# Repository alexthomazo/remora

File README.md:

Remora
======

Contrôleur fil pilote permettant de contrôler 7 zones et un relai.

Basé sur ESP32 et ESPHome.

Version 2.0 de Remora basé sur https://github.com/tducret/programmateur-fil-pilote-wifi/tree/master

Fonctionnalités
---------------

 * ESP32 Mini D1
 * MCP23017 pour le contrôle des 7 zones et du relai
 * Port ethernet optionnel
 * Connecteur I2C pour ecran OLED
 * Relai permettant le contrôle d'un connecteur heures pleines/creuses

Changements depuis la version 1.3
---------------------------------

 * Ajout
   - Ajout d'un condensateur 47u en entrée pour filtrage
   - Port Ethernet (optionnel)
   - Snubber RC pour maximiser la durée de vie du relai
   - LED "relai" indépendante

 * Modification
   - Base ESP32 D1 mini
   - MCP23017 en SMD pour gain de place
   - Téléinfo basée sur Denky D4 avec résistance variable et LED
   - Nouvelle ref opto fils pilotes TLP267J
   - Nouvelle ref relai G5Q-1 (mécanique moins cher SSR) 
   
 * Suppression
   - récepteurs sans fils 433 et 868Mhz
   - connecteurs SPI et Groove I2C
   - LED 3mm RGB

Les composants SMD (hors partie LAN) sont prévus pour être soudés au fer.

Schématique
-----------

Board
-----

Case
----

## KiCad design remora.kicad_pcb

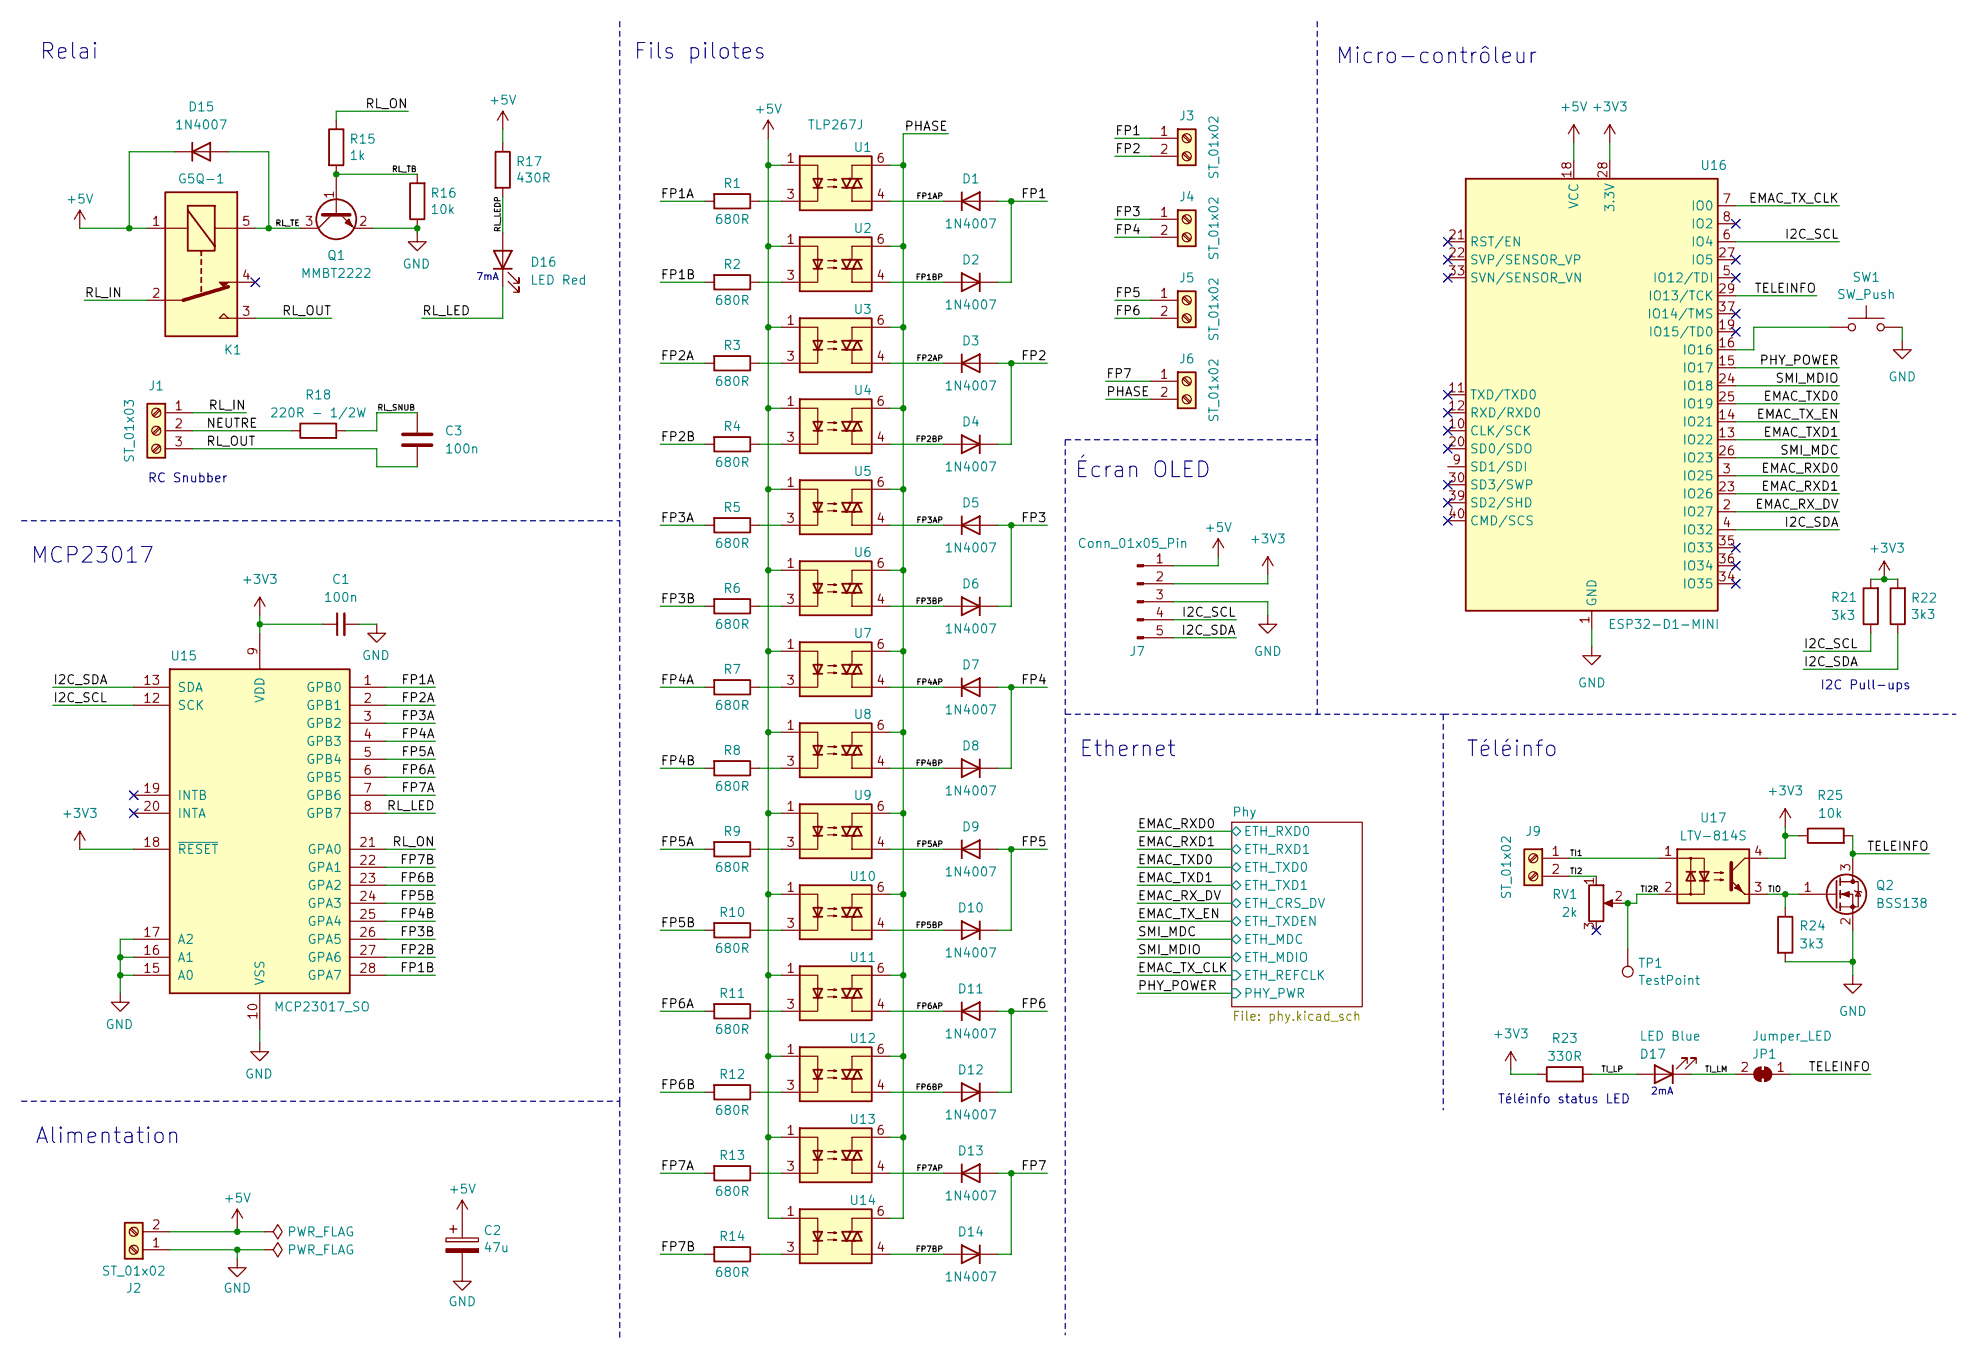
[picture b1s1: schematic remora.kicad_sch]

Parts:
C1: 100n; C_0805_2012Metric_Pad1.18x1.45mm_HandSolder; Mouser# 603-CC805KRX7R9BB104; LCSC# C49678
C2: 47u; C_Elec_6.3x5.4; Mouser# 80-EDK476M035A9GAA; LCSC# C131122
C3: 100n; C_Rect_L11.5mm_W5.6mm_P10.00mm_MKT; LCSC# C506867
D1, D2, D3, D4, D5, D6, D7, D8, D9, D10, D11, D12, D13, D14, D15: 1N4007; D_SOD-123FL; Mouser# 863-NRVS1MFL; LCSC# C727082
D16: LED Red; LED_0805_2012Metric_Pad1.15x1.40mm_HandSolder; Mouser# 743-IN-S85AT5UW; LCSC# C7371913
D17: LED Blue; LED_0805_2012Metric_Pad1.15x1.40mm_HandSolder; Mouser# 743-IN-S85AT5B; LCSC# C434433
J1: ST_01x03; TerminalBlock_Phoenix_PT-1,5-3-5.0-H_1x03_P5.00mm_Horizontal; Mouser# 490-TB003-500-P03BE; LCSC# C5188464
J2, J3, J4, J5, J6, J9: ST_01x02; TerminalBlock_Phoenix_PT-1,5-2-5.0-H_1x02_P5.00mm_Horizontal; Mouser# 490-TB003-500-P02BE; LCSC# C5188463
J7: Conn_01x05_Pin; PinHeader_1x05_P2.54mm_Vertical; Mouser# 200-EW0509TS300; LCSC# C492404
JP1: Jumper_LED; SolderJumper-2_P1.3mm_Bridged_RoundedPad1.0x1.5mm
K1: G5Q-1; Relay_SPDT_Omron-G5Q-1; Mouser# 769-ALQ105; LCSC# C719517
Q1: MMBT2222; SOT-23; Mouser# 771-MMBT2222A215; LCSC# C916372
Q2: BSS138; SOT-23; Mouser# 771-BSS138P215; LCSC# C713688
R1, R2, R3, R4, R5, R6, R7, R8, R9, R10, R11, R12, R13, R14: 680R; R_0805_2012Metric_Pad1.20x1.40mm_HandSolder; Mouser# 603-RC0805FR-07680RL; LCSC# C114549
R15: 1k; R_0805_2012Metric_Pad1.20x1.40mm_HandSolder; Mouser# 603-RC0805FR-071KL
R16, R25: 10k; R_0805_2012Metric_Pad1.20x1.40mm_HandSolder; Mouser# 603-RC0805FR-0710KL
R17: 430R; R_0805_2012Metric_Pad1.20x1.40mm_HandSolder; Mouser# 603-RC0805FR-07430RL
R18: 220R - 1/2W; R_Axial_DIN0309_L9.0mm_D3.2mm_P12.70mm_Horizontal; Mouser# 603-CFR-50JR-52-220R; LCSC# C119410
R21, R22, R24: 3k3; R_0805_2012Metric_Pad1.20x1.40mm_HandSolder; Mouser# 603-RC0805FR-073K3L
R23: 330R; R_0805_2012Metric_Pad1.20x1.40mm_HandSolder; Mouser# 603-RC0805FR-07330RL; LCSC# C105878
RV1: 2k; Potentiometer_Bourns_TC33X_Vertical; Mouser# 652-TC33X-2-202E; LCSC# C128549
SW1: SW_Push; SW_Push_1P1T_NO_6x6mm_H9.5mm; Mouser# 179-TS046655BK160SMT; LCSC# C255812
TP1: TestPoint; TestPoint_THTPad_D1.0mm_Drill0.5mm
U1, U2, U3, U4, U5, U6, U7, U8, U9, U10, U11, U12, U13, U14: TLP267J; MFSOP6-4_4.4x3.6mm_P1.27mm; Mouser# 757-TLP267JE; LCSC# C393892
U15: MCP23017_SO; SOIC-28W_7.5x17.9mm_P1.27mm; Mouser# 579-MCP23017-E/SO; LCSC# C629440
U16: ESP32-D1-MINI
U17: LTV-814S; DIP-4_W8.89mm_SMDSocket_LongPads; Mouser# 859-LTV-814S; LCSC# C125118

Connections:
+3V3: C1.1, J7.2, R21.2, R22.2, R23.1, R25.1, U15.9 (VDD), U15.18 (~RESET), U16.28 (3.3V), U17.4; also elsewhere on the board
+5V: C2.1, D15.1 (K), J2.2, J7.1, K1.1, R17.1, U1.1, U2.1, U3.1, U4.1, U5.1, U6.1, U7.1, U8.1, U9.1, U10.1, U11.1, U12.1, U13.1, U14.1, U16.18 (VCC)
/EMAC_RXD0: U16.3 (IO25); also elsewhere on the board
/EMAC_RXD1: U16.23 (IO26); also elsewhere on the board
/EMAC_RX_DV: U16.2 (IO27); also elsewhere on the board
/EMAC_TXD0: U16.25 (IO19); also elsewhere on the board
/EMAC_TXD1: U16.13 (IO22); also elsewhere on the board
/EMAC_TX_CLK: U16.7 (IO0); also elsewhere on the board
/EMAC_TX_EN: U16.14 (IO21); also elsewhere on the board
/FP1: D1.2 (A), D2.1 (K), J3.1
/FP1A: R1.2, U15.1 (GPB0)
/FP1AP: D1.1 (K), U1.4
/FP1B: R2.2, U15.28 (GPA7)
/FP1BP: D2.2 (A), U2.4
/FP2: D3.2 (A), D4.1 (K), J3.2
/FP2A: R3.2, U15.2 (GPB1)
/FP2AP: D3.1 (K), U3.4
/FP2B: R4.2, U15.27 (GPA6)
/FP2BP: D4.2 (A), U4.4
/FP3: D5.2 (A), D6.1 (K), J4.1
/FP3A: R5.2, U15.3 (GPB2)
/FP3AP: D5.1 (K), U5.4
/FP3B: R6.2, U15.26 (GPA5)
/FP3BP: D6.2 (A), U6.4
/FP4: D7.2 (A), D8.1 (K), J4.2
/FP4A: R7.2, U15.4 (GPB3)
/FP4AP: D7.1 (K), U7.4
/FP4B: R8.2, U15.25 (GPA4)
/FP4BP: D8.2 (A), U8.4
/FP5: D9.2 (A), D10.1 (K), J5.1
/FP5A: R9.2, U15.5 (GPB4)
/FP5AP: D9.1 (K), U9.4
/FP5B: R10.2, U15.24 (GPA3)
/FP5BP: D10.2 (A), U10.4
/FP6: D11.2 (A), D12.1 (K), J5.2
/FP6A: R11.2, U15.6 (GPB5)
/FP6AP: D11.1 (K), U11.4
/FP6B: R12.2, U15.23 (GPA2)
/FP6BP: D12.2 (A), U12.4
/FP7: D13.2 (A), D14.1 (K), J6.1
/FP7A: R13.2, U15.7 (GPB6)
/FP7AP: D13.1 (K), U13.4
/FP7B: R14.2, U15.22 (GPA1)
/FP7BP: D14.2 (A), U14.4
/I2C_SCL: J7.4, R21.1, U15.12 (SCK), U16.6 (IO4)
/I2C_SDA: J7.5, R22.1, U15.13 (SDA), U16.4 (IO32)
/NEUTRE: J1.2, R18.1
/PHASE: J6.2, U1.6, U2.6, U3.6, U4.6, U5.6, U6.6, U7.6, U8.6, U9.6, U10.6, U11.6, U12.6, U13.6, U14.6
/PHY_POWER: U16.15 (IO17); also elsewhere on the board
/RL_IN: J1.1, K1.2
/RL_LED: D16.1 (K), U15.8 (GPB7)
/RL_LEDP: D16.2 (A), R17.2
/RL_ON: R15.1, U15.21 (GPA0)
/RL_OUT: C3.1, J1.3, K1.3
/RL_SNUB: C3.2, R18.2
/RL_TB: Q1.1 (B), R15.2, R16.2
/RL_TE: D15.2 (A), K1.5, Q1.3 (C)
/SMI_MDC: U16.26 (IO23); also elsewhere on the board
/SMI_MDIO: U16.24 (IO18); also elsewhere on the board
/TELEINFO: JP1.1 (A), Q2.3 (D), R25.2, U16.29 (IO13/TCK)
/TI1: J9.1, U17.1
/TI2: J9.2, RV1.1
/TI2R: RV1.2, TP1.1, U17.2
/TIO: Q2.1 (G), R24.1, U17.3
/TI_LM: D17.1 (K), JP1.2 (B)
/TI_LP: D17.2 (A), R23.2
GND: C1.2, C2.2, J2.1, J7.3, Q1.2 (E), Q2.2 (S), R16.1, R24.2, SW1.2, U15.10 (VSS), U15.15 (A0), U15.16 (A1), U15.17 (A2), U16.1 (GND), U16.17 (GND), U16.31 (GND); also elsewhere on the board
unnamed: R1.1, U1.3
unnamed: R2.1, U2.3
unnamed: R3.1, U3.3
unnamed: R4.1, U4.3
unnamed: R5.1, U5.3
unnamed: R6.1, U6.3
unnamed: R7.1, U7.3
unnamed: R8.1, U8.3
unnamed: R9.1, U9.3
unnamed: R10.1, U10.3
unnamed: R11.1, U11.3
unnamed: R12.1, U12.3
unnamed: R13.1, U13.3
unnamed: R14.1, U14.3
unnamed: SW1.1, U16.16 (IO16)

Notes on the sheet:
7mA
MCP23017
Relai
2mA
Écran OLED
Fils pilotes
Alimentation
RC Snubber
Téléinfo
I2C Pull-ups
Ethernet
Téléinfo status LED
Micro-contrôleur

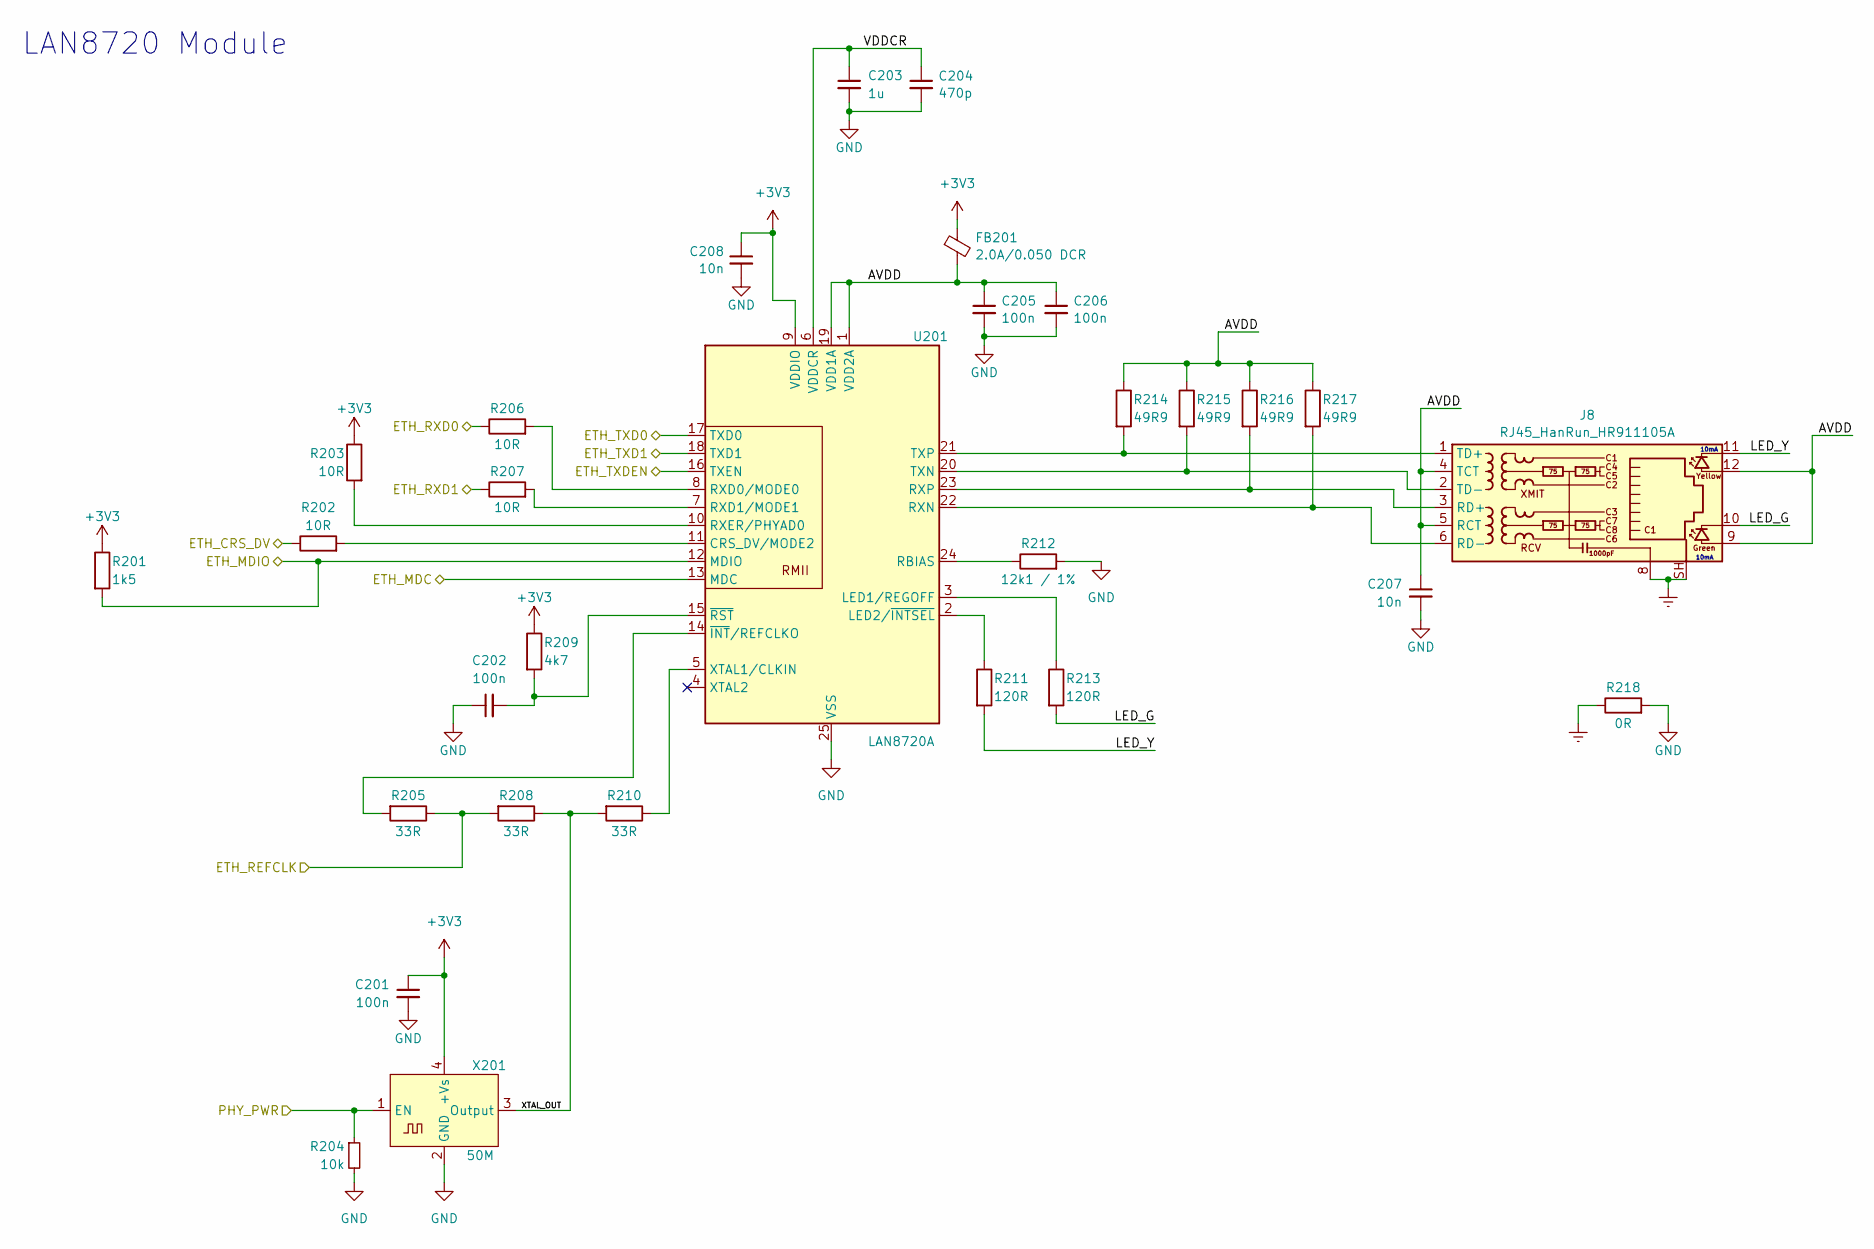
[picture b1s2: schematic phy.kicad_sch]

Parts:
C201, C202, C205, C206: 100n; C_0805_2012Metric_Pad1.18x1.45mm_HandSolder; Mouser# 603-CC805KRX7R9BB104; LCSC# C49678
C203: 1u; C_0805_2012Metric_Pad1.18x1.45mm_HandSolder; Mouser# 603-CC805KKX7R9BB105; LCSC# C91185
C204: 470p; C_0805_2012Metric_Pad1.18x1.45mm_HandSolder; Mouser# 603-CC805KRX7R9BB471; LCSC# C107152
C207, C208: 10n; C_0805_2012Metric_Pad1.18x1.45mm_HandSolder; Mouser# 603-CC805KRX7R9BB103; LCSC# C83170
FB201: 2.0A/0.050 DCR; L_0805_2012Metric_Pad1.15x1.40mm_HandSolder; Mouser# 81-BLM21SN300SN1D; LCSC# C596496
J8: RJ45_HanRun_HR911105A; RJ45_Hanrun_HR911105A_Horizontal; LCSC# C12074
R201: 1k5; R_0805_2012Metric_Pad1.20x1.40mm_HandSolder; Mouser# 603-RC0805FR-071K5L; LCSC# C114555
R202, R203, R206, R207: 10R; R_0805_2012Metric_Pad1.20x1.40mm_HandSolder; Mouser# 603-RC0805FR-0710RL; LCSC# C96347
R204: 10k; R_0805_2012Metric_Pad1.20x1.40mm_HandSolder; Mouser# 603-RC0805FR-0710KL
R205, R208, R210: 33R; R_0805_2012Metric_Pad1.20x1.40mm_HandSolder; Mouser# 603-RC0805FR-0733RL; LCSC# C126353
R209: 4k7; R_0805_2012Metric_Pad1.20x1.40mm_HandSolder; Mouser# 603-RC0805FR-074K7L; LCSC# C60816
R211, R213: 120R; R_0805_2012Metric_Pad1.20x1.40mm_HandSolder; Mouser# 603-RC0805FR-07120RL; LCSC# C114245
R212: 12k1 / 1%; R_0805_2012Metric_Pad1.20x1.40mm_HandSolder; Mouser# 603-RC0805FR-0712K1L; LCSC# C2933295
R214, R215, R216, R217: 49R9; R_0805_2012Metric_Pad1.20x1.40mm_HandSolder; Mouser# 603-RC0805FR-0749R9L; LCSC# C132320
R218: 0R; R_0805_2012Metric_Pad1.20x1.40mm_HandSolder; Mouser# 603-RC0805FR-070RL; LCSC# C96345
U201: LAN8720A; VQFN-24-1EP_4x4mm_P0.5mm_EP2.5x2.5mm; Mouser# 886-LAN8720A-CP-TR; LCSC# C45223
X201: 50M; Oscillator_SMD_Abracon_ASV-4Pin_7.0x5.1mm; Mouser# 815-ASV-50.000M-E-T; LCSC# C242207

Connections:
+3V3: C201.1, C208.1, FB201.1, R201.1, R203.1, R209.1, U201.9 (VDDIO), X201.4 (+Vs); also elsewhere on the board
/EMAC_RXD0: R206.1; also elsewhere on the board
/EMAC_RXD1: R207.1; also elsewhere on the board
/EMAC_RX_DV: R202.1; also elsewhere on the board
/EMAC_TXD0: U201.17 (TXD0); also elsewhere on the board
/EMAC_TXD1: U201.18 (TXD1); also elsewhere on the board
/EMAC_TX_CLK: R205.1, R208.2; also elsewhere on the board
/EMAC_TX_EN: U201.16 (TXEN); also elsewhere on the board
/PHY_POWER: R204.1, X201.1 (EN); also elsewhere on the board
/Phy/AVDD: C205.1, C206.1, C207.1, FB201.2, J8.4 (TCT), J8.5 (RCT), J8.9, J8.12, R214.1, R215.1, R216.1, R217.1, U201.1 (VDD2A), U201.19 (VDD1A)
/Phy/LED_G: J8.10, R213.2
/Phy/LED_Y: J8.11, R211.2
/Phy/VDDCR: C203.1, C204.1, U201.6 (VDDCR)
/Phy/XTAL_OUT: R208.1, R210.2, X201.3 (Output)
/SMI_MDC: U201.13 (MDC); also elsewhere on the board
/SMI_MDIO: R201.2, U201.12 (MDIO); also elsewhere on the board
Earth: J8.8, J8.SH, R218.1
GND: C201.2, C202.1, C203.2, C204.2, C205.2, C206.2, C207.2, C208.2, R204.2, R212.2, R218.2, U201.25 (VSS), X201.2 (GND); also elsewhere on the board
unnamed: J8.3 (RD+), R216.2, U201.23 (RXP)
unnamed: J8.6 (RD-), R217.2, U201.22 (RXN)
unnamed: J8.1 (TD+), R214.2, U201.21 (TXP)
unnamed: J8.2 (TD-), R215.2, U201.20 (TXN)
unnamed: R202.2, U201.11 (CRS_DV/MODE2)
unnamed: R213.1, U201.3 (LED1/REGOFF)
unnamed: R211.1, U201.2 (LED2/~INTSEL)
unnamed: R212.1, U201.24 (RBIAS)
unnamed: R206.2, U201.8 (RXD0/MODE0)
unnamed: R207.2, U201.7 (RXD1/MODE1)
unnamed: R203.2, U201.10 (RXER/PHYAD0)
unnamed: R210.1, U201.5 (XTAL1/CLKIN)
unnamed: R205.2, U201.14 (~INT/REFCLKO)
unnamed: C202.2, R209.2, U201.15 (~RST)

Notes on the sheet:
10mA
LAN8720 Module

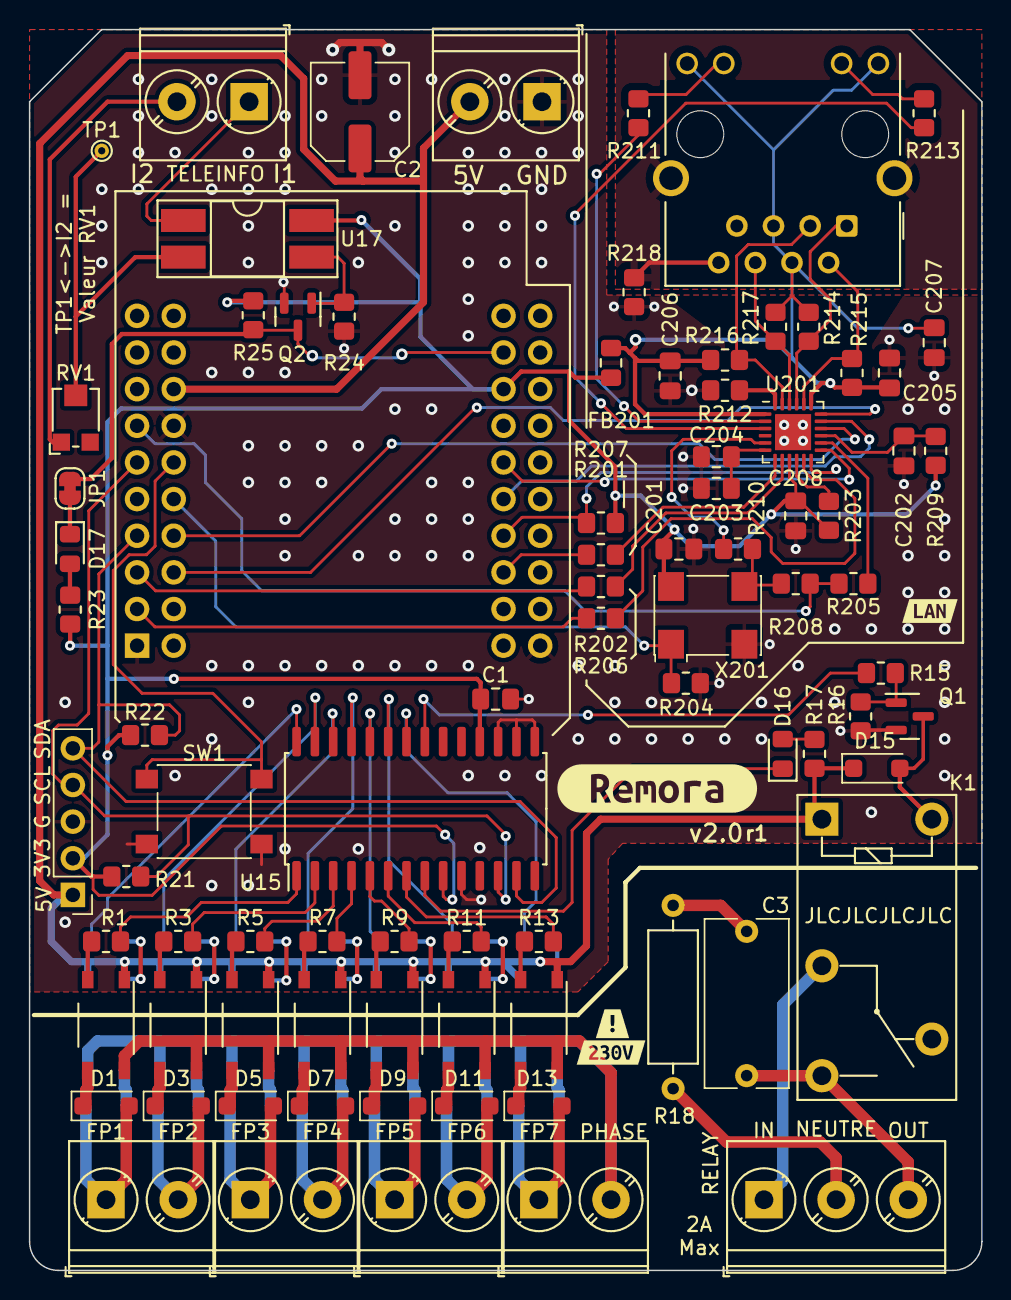
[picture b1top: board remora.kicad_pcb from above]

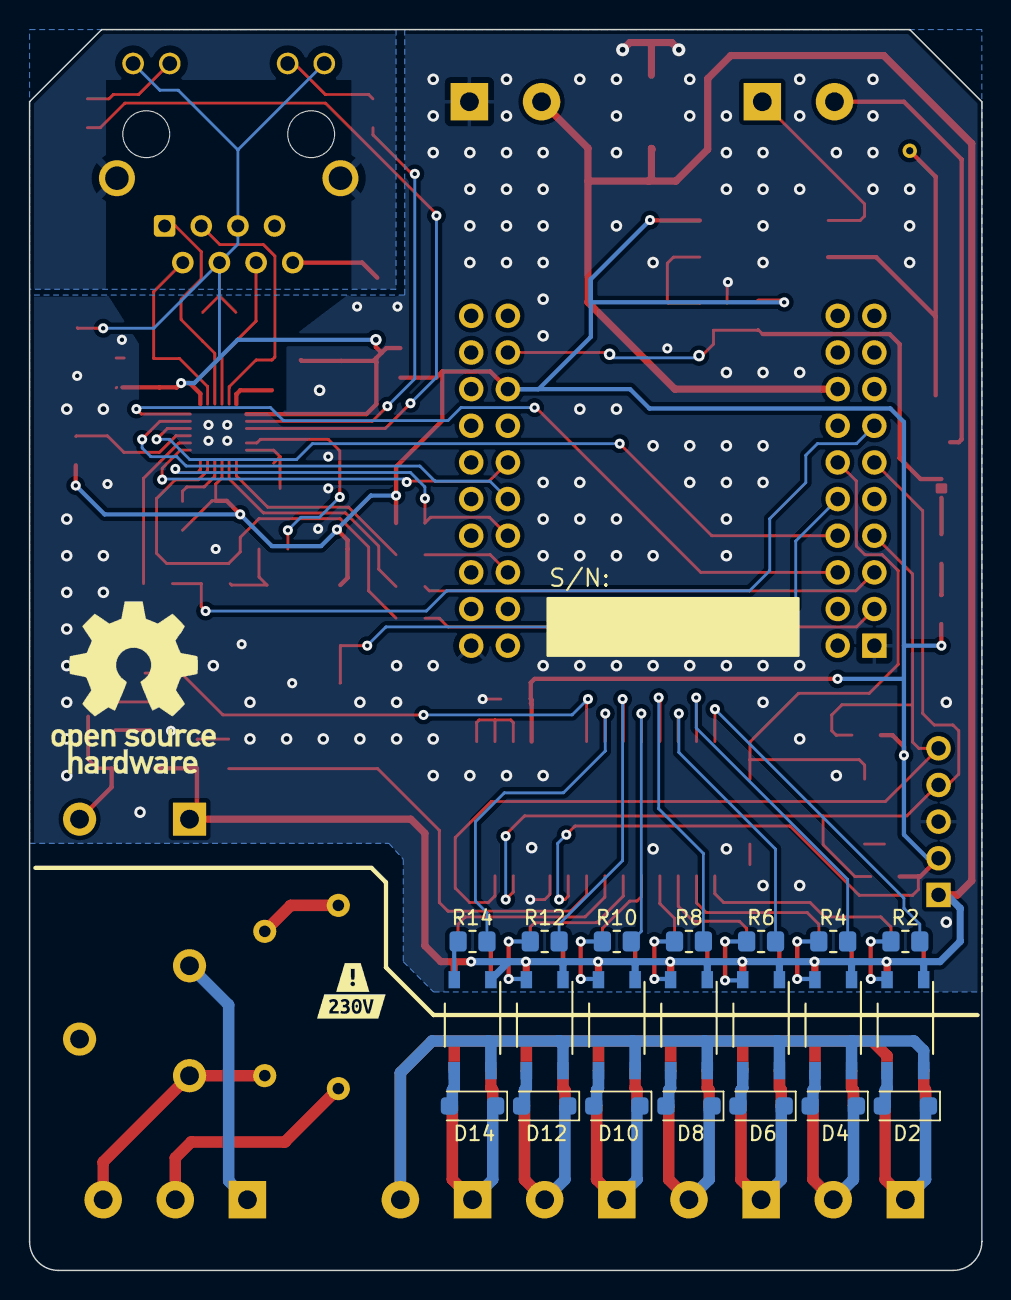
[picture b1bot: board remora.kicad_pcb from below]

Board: 2 copper layers, 66.0 x 86.0 mm, 111 parts (23 on the bottom side), 102 nets.

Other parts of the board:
kibuzzard-65A3E6CE, kibuzzard-65A3E6CE#2: G***; kibuzzard-65A3E6CE
kibuzzard-65A3E49B, kibuzzard-65A3E49B#2: G***; kibuzzard-65A3E49B
kibuzzard-659BD475: G***; kibuzzard-659BD475
kibuzzard-659BD659: G***; kibuzzard-659BD659

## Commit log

2024-01-14 Ajout version 2.0
2024-01-28 Add Switch
2024-01-28 Modif commande v2.0
2024-02-25 Mise a jour resistance puissance LED
2024-02-26 Mise a jour 1er assemblage
2024-03-02 Fix transistor relai (collecteur et émeteur intervertis)
2024-07-14 Deplacement du pin teleinfo de SD1 à GPIO13
2024-07-25 Ajout de la configuration ESPHome
2024-08-28 Nouvelles empreintes pour les diodes
    Les pads des diodes ont été agrandies et espacées pour respecter la datasheet.
    Changement ref des borniers pour du 2.5mm²
2024-08-28 Version 2.0 r1

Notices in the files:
remora.kicad_sch:
CC BY-NC-SA 4.0
